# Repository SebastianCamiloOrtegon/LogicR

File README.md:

# **LOGICR**_
* **L**ogica
* **O**rientada para 
* **G**enerar
* **I**nstrucciones en 
* **C**odigo con
* **R**obotica

# Integrantes
* Bayron Andrés Pedraza Ramirez
* Sebastian Camilo Ortegón Hernandez
* Oscar Santiago Serrano Cipriam

# Descripción y/o Introducción
En  los  últimos  años  nos  encontramos  en  la  Cuarta Revolución  Industrial,  donde  la  automatización  y  la inteligencia  artificial  están  transformando  el  mundo laboral  que  conlleva  desafíos  como:  el  desempleo,  el agotamiento de los recursos y el cambio climático. Frente a  esto,  estamos  viviendo  la  transición  a  la  Quinta Revolución Industrial que busca equilibrar la tecnología y el ingenio humano, preparándonos para un futuro más sostenible e innovador.
Nuestro proyecto, Logic R, surge con la misión de preparar a las futuras generaciones para este nuevo escenario.
Acercando a los niños al mundo de la tecnología por medio de nuestro proyecto que se puede mover por medio de una aplicacion WIFI, pueden interactuar con el proyecto que cuenta con ruedas omnidireccionales para desplazarse en varias direcciones, un brazo mecanico con una garra que permite trasladar objetos pequeños y un sensor ultrasonido el cual permite medir la distancia entre el LOGICR y los objetos que esten frente a este.
Gracias al proyecto los niños de manera intuitiva pueden aprender sobre logica de programación, desarrollar habilidades logicas y poder resolver problemas que requieren logica basica por medio de este proyecto.

# Poster o Brochure

# Imagen tipo banner de la implementación del proyecto (resultado final)

# Vídeo final del proyecto:
https://www.youtube.com/watch?v=GcuSlTJKFjA

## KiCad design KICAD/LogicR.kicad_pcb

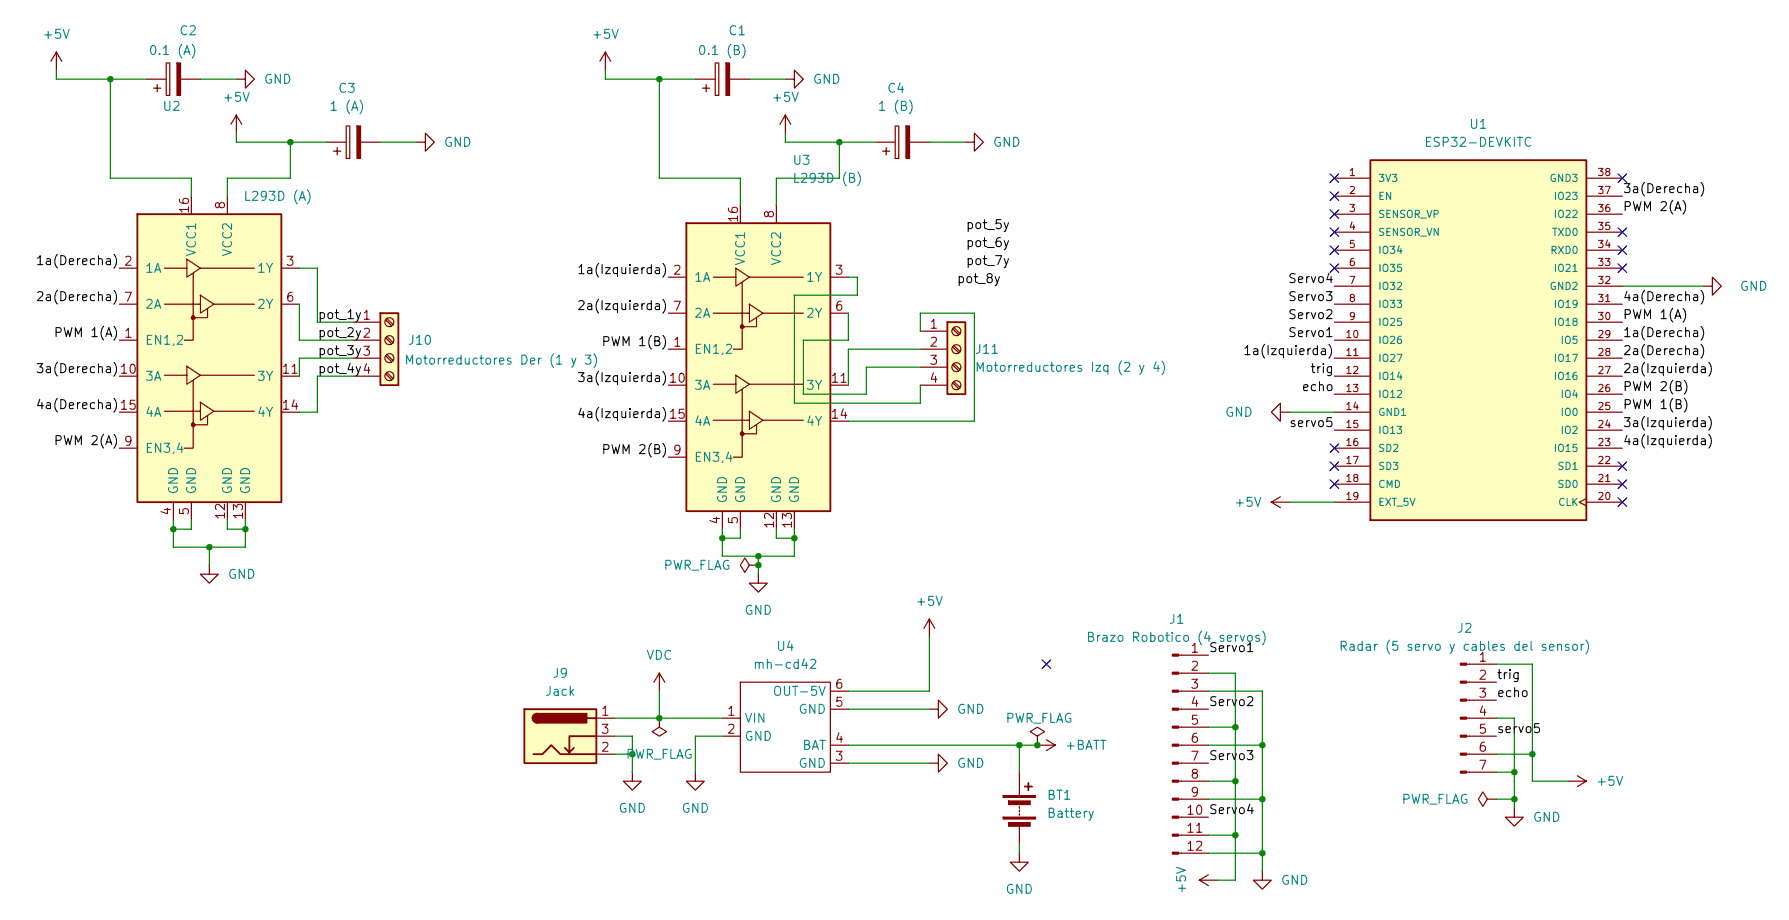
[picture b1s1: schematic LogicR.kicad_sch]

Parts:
BT1: Battery; TerminalBlock_bornier-2_P5.08mm
C1: 0.1 (B); CP_Radial_D5.0mm_P2.00mm
C2: 0.1 (A); CP_Radial_D5.0mm_P2.00mm
C3: 1 (A); CP_Radial_D5.0mm_P2.00mm
C4: 1 (B); CP_Radial_D5.0mm_P2.00mm
J1: Brazo Robotico (4 servos); PinHeader_1x12_P2.54mm_Vertical
J2: Radar (5 servo y cables del sensor); PinHeader_1x07_P2.54mm_Vertical
J9: Jack; BarrelJack_Horizontal
J10: Motorreductores Der (1 y 3); TerminalBlock_bornier-4_P5.08mm
J11: Motorreductores Izq (2 y 4); TerminalBlock_bornier-4_P5.08mm
U1: ESP32-DEVKITC; MODULE_ESP32-DEVKITC; PARTREV N/A
U2: L293D (A); DIP-16_W7.62mm
U3: L293D (B); DIP-16_W7.62mm
U4: mh-cd42

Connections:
+5V: C1.1, C2.1, C3.1, C4.1, J1.2, J1.5, J1.8, J1.11, J2.1, J2.6, U1.19 (EXT_5V), U2.8 (VCC2), U2.16 (VCC1), U3.8 (VCC2), U3.16 (VCC1), U4.6 (OUT-5V)
+BATT: BT1.1 (+), U4.4 (BAT)
/1a(Derecha): U1.29 (IO5), U2.2 (1A)
/1a(Izquierda): U1.11 (IO27), U3.2 (1A)
/2a(Derecha): U1.28 (IO17), U2.7 (2A)
/2a(Izquierda): U1.27 (IO16), U3.7 (2A)
/3a(Derecha): U1.37 (IO23), U2.10 (3A)
/3a(Izquierda): U1.24 (IO2), U3.10 (3A)
/4a(Derecha): U1.31 (IO19), U2.15 (4A)
/4a(Izquierda): U1.23 (IO15), U3.15 (4A)
/PWM 1(A): U1.30 (IO18), U2.1 (EN1,2)
/PWM 1(B): U1.25 (IO0), U3.1 (EN1,2)
/PWM 2(A): U1.36 (IO22), U2.9 (EN3,4)
/PWM 2(B): U1.26 (IO4), U3.9 (EN3,4)
/Servo1: J1.1, U1.10 (IO26)
/Servo2: J1.4, U1.9 (IO25)
/Servo3: J1.7, U1.8 (IO33)
/Servo4: J1.10, U1.7 (IO32)
/echo: J2.3, U1.13 (IO12)
/pot_1y: J10.1, U2.3 (1Y)
/pot_2y: J10.2, U2.6 (2Y)
/pot_3y: J10.3, U2.11 (3Y)
/pot_4y: J10.4, U2.14 (4Y)
/servo5: J2.5, U1.15 (IO13)
/trig: J2.2, U1.12 (IO14)
GND: BT1.2 (-), C1.2, C2.2, C3.2, C4.2, J1.3, J1.6, J1.9, J1.12, J2.4, J2.7, J9.2, J9.3, U1.14 (GND1), U1.32 (GND2), U2.4 (GND), U2.5 (GND), U2.12 (GND), U2.13 (GND), U3.4 (GND), U3.5 (GND), U3.12 (GND), U3.13 (GND), U4.2 (GND), U4.3 (GND), U4.5 (GND)
unnamed: J11.1, U3.14 (4Y)
unnamed: J11.2, U3.11 (3Y)
unnamed: J11.3, U3.6 (2Y)
unnamed: J11.4, U3.3 (1Y)
VDC: J9.1, U4.1 (VIN)

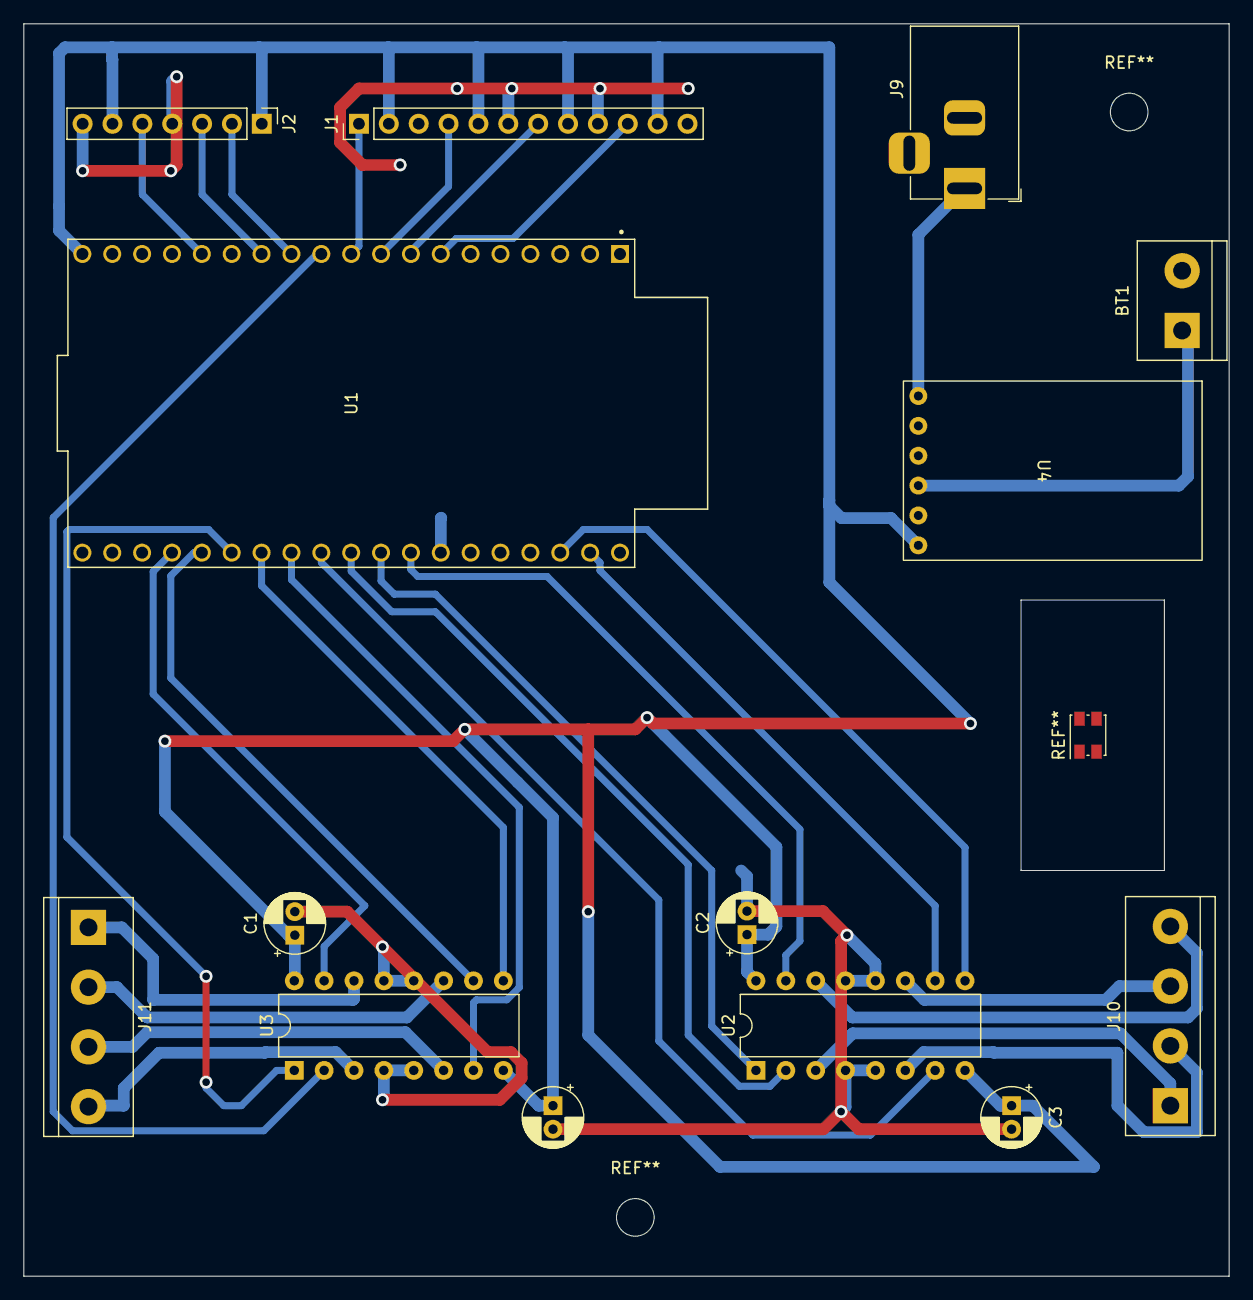
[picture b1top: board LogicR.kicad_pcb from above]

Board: 2 copper layers, 102.5 x 106.5 mm, 14 parts (0 on the bottom side), 31 nets.

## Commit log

2024-09-23 Rename Beige Red Black Illustrative Basketball Tournament Poster.png to POSTER LOGICR
2024-09-25 Create Archivos impresión 3D
2024-09-25 Create prueba
2024-09-25 Create a
2024-09-26 Create b
2024-09-26 Create Archivos principales
2024-09-26 Create Servomotor sg90
